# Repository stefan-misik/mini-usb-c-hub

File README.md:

# Mini USB-C Hub

Miniature USB-C hub to attach to your keyboard so you can share one wire for
mouse and keyboard. This hub uses FE1.1s USB 2.0 hub IC.

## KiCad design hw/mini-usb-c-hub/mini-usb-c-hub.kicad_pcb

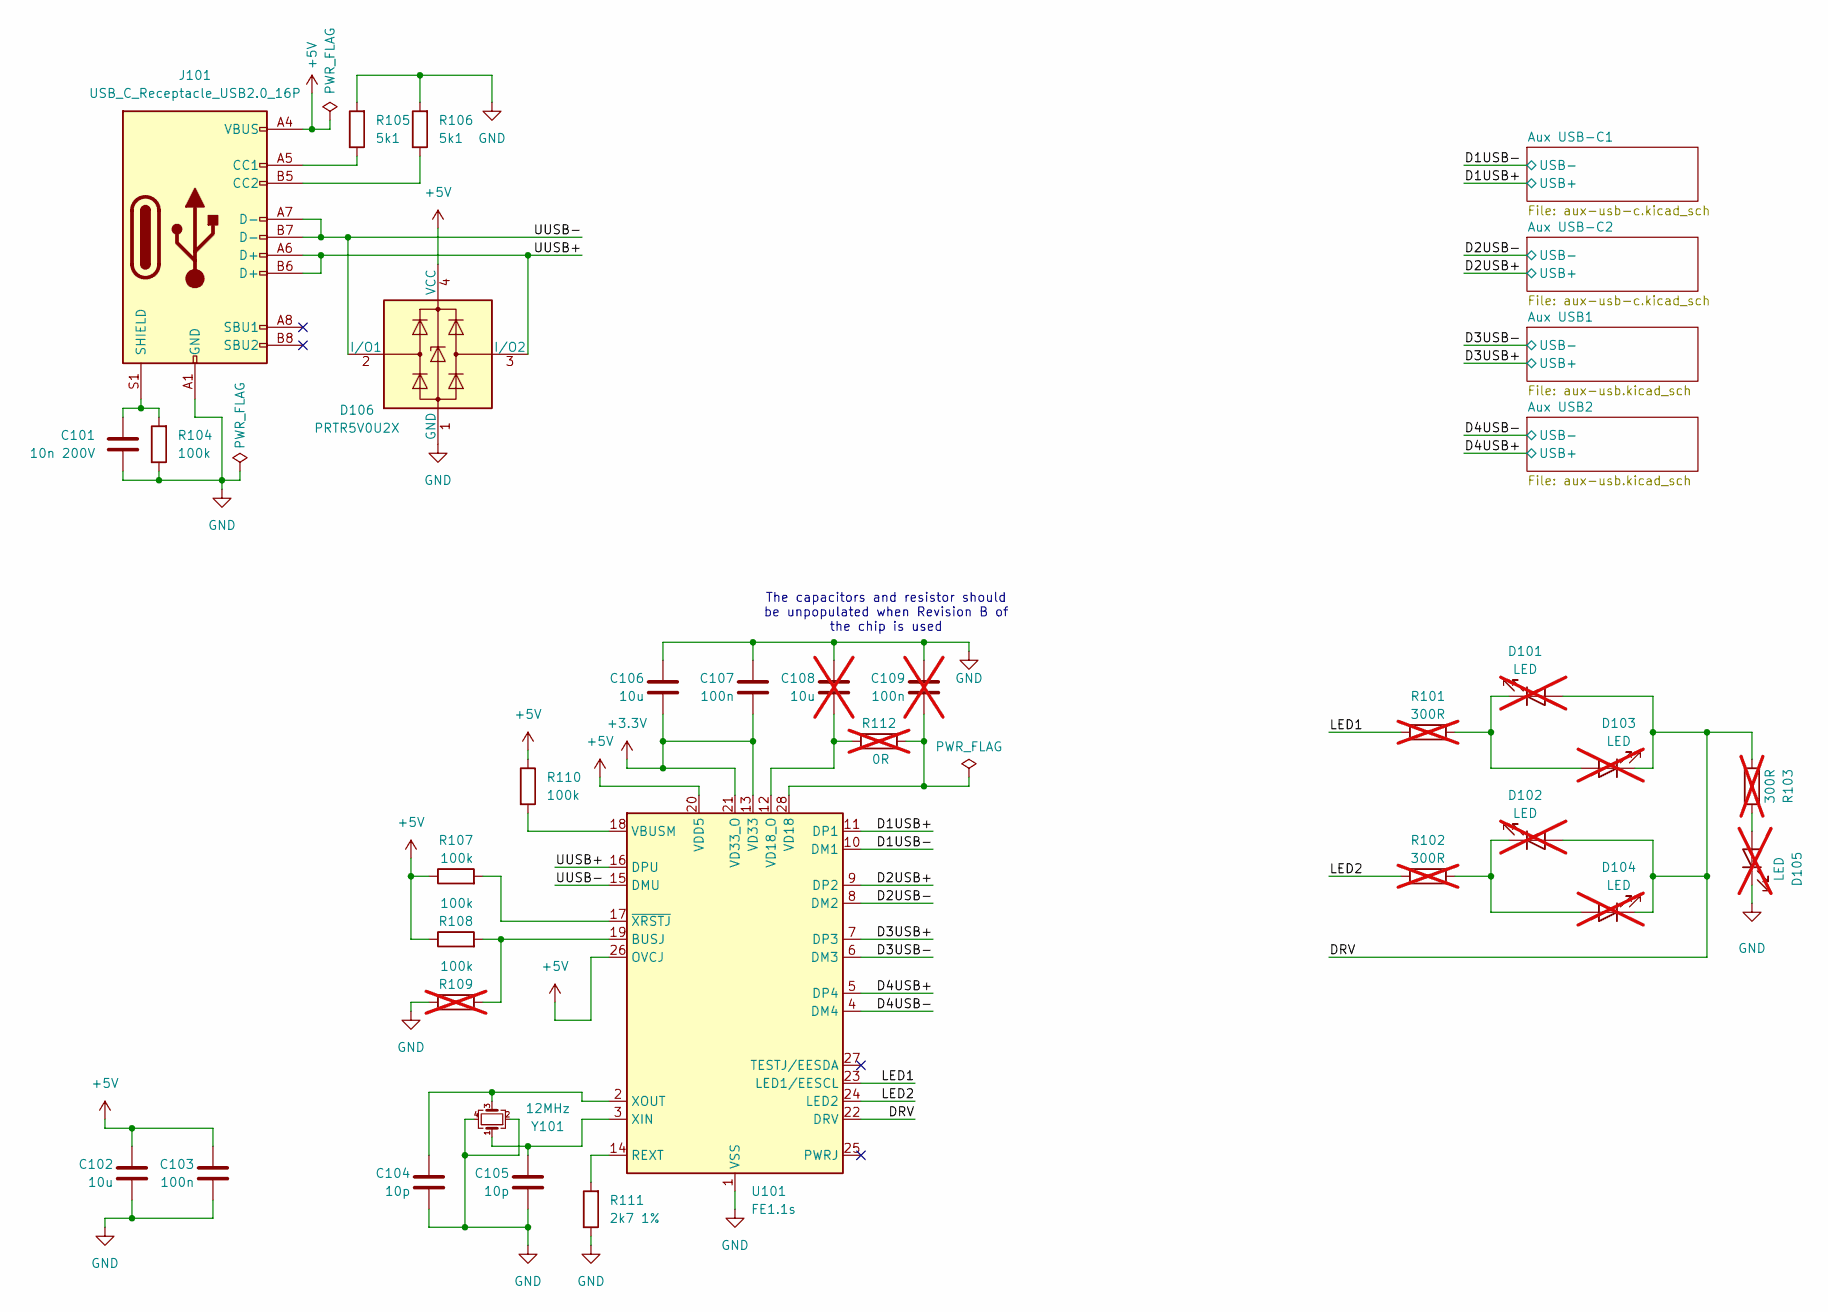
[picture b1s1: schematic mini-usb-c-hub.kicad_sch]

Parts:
C101: 10n 200V; C_0805_2012Metric_Pad1.18x1.45mm_HandSolder
C102, C106: 10u; C_1206_3216Metric_Pad1.33x1.80mm_HandSolder
C103, C107: 100n; C_0805_2012Metric_Pad1.18x1.45mm_HandSolder
C104, C105: 10p; C_0805_2012Metric_Pad1.18x1.45mm_HandSolder
C108: 10u; C_1206_3216Metric_Pad1.33x1.80mm_HandSolder; not fitted
C109: 100n; C_0805_2012Metric_Pad1.18x1.45mm_HandSolder; not fitted
D101, D102, D103, D104, D105: LED; LED_0805_2012Metric_Pad1.15x1.40mm_HandSolder; not fitted
D106: PRTR5V0U2X; SOT-143
J101: USB_C_Receptacle_USB2.0_16P; USB_C_Receptacle_G-Switch_GT-USB-7010ASV_shortened
R101, R102, R103: 300R; R_0805_2012Metric_Pad1.20x1.40mm_HandSolder; not fitted
R104, R107, R108, R110: 100k; R_0805_2012Metric_Pad1.20x1.40mm_HandSolder
R105, R106: 5k1; R_0805_2012Metric_Pad1.20x1.40mm_HandSolder
R109: 100k; R_0805_2012Metric_Pad1.20x1.40mm_HandSolder; not fitted
R111: 2k7 1%; R_0805_2012Metric_Pad1.20x1.40mm_HandSolder
R112: 0R; R_0805_2012Metric_Pad1.20x1.40mm_HandSolder; not fitted
U101: FE1.1s; SSOP-28_3.9x9.9mm_P0.635mm
Y101: 12MHz; Crystal_SMD_3225-4Pin_3.2x2.5mm_HandSoldering

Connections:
+3.3V: C106.1, C107.1, U101.13 (VD33), U101.21 (VD33_O)
+5V: C102.2, C103.2, D106.4 (VCC), J101.A4 (VBUS), J101.A9 (VBUS), J101.B4 (VBUS), J101.B9 (VBUS), R107.1, R108.1, R110.1, U101.20 (VDD5), U101.26 (OVCJ); also elsewhere on the board
/D1USB+: U101.11 (DP1); also elsewhere on the board
/D1USB-: U101.10 (DM1); also elsewhere on the board
/D2USB+: U101.9 (DP2); also elsewhere on the board
/D2USB-: U101.8 (DM2); also elsewhere on the board
/D3USB+: U101.7 (DP3); also elsewhere on the board
/D3USB-: U101.6 (DM3); also elsewhere on the board
/D4USB+: U101.5 (DP4); also elsewhere on the board
/D4USB-: U101.4 (DM4); also elsewhere on the board
/DRV: D101.2 (A), D102.2 (A), D103.1 (K), D104.1 (K), R103.1, U101.22 (DRV)
/LED1: R101.1, U101.23 (LED1/EESCL)
/LED2: R102.1, U101.24 (LED2)
/UUSB+: D106.3 (I/O2), J101.A6 (D+), J101.B6 (D+), U101.16 (DPU)
/UUSB-: D106.2 (I/O1), J101.A7 (D-), J101.B7 (D-), U101.15 (DMU)
GND: C101.1, C102.1, C103.1, C104.1, C105.1, C106.2, C107.2, C108.2, C109.2, D105.1 (K), D106.1 (GND), J101.A1 (GND), J101.A12 (GND), J101.B1 (GND), J101.B12 (GND), R104.1, R105.2, R106.2, R109.1, R111.1, U101.1 (VSS), Y101.2, Y101.4; also elsewhere on the board
unnamed: D101.1 (K), D103.2 (A), R101.2
unnamed: D102.1 (K), D104.2 (A), R102.2
unnamed: D105.2 (A), R103.2
unnamed: J101.A5 (CC1), R105.1
unnamed: J101.B5 (CC2), R106.1
unnamed: C101.2, J101.S1 (SHIELD), R104.2
unnamed: R108.2, R109.2, U101.19 (BUSJ)
unnamed: R111.2, U101.14 (REXT)
unnamed: R110.2, U101.18 (VBUSM)
unnamed: C109.1, R112.2, U101.28 (VD18)
unnamed: C108.1, R112.1, U101.12 (VD18_O)
unnamed: C105.2, U101.3 (XIN), Y101.1
unnamed: C104.2, U101.2 (XOUT), Y101.3
unnamed: R107.2, U101.17 (~XRSTJ)

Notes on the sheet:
The capacitors and resistor should be unpopulated when Revision B of the chip is used

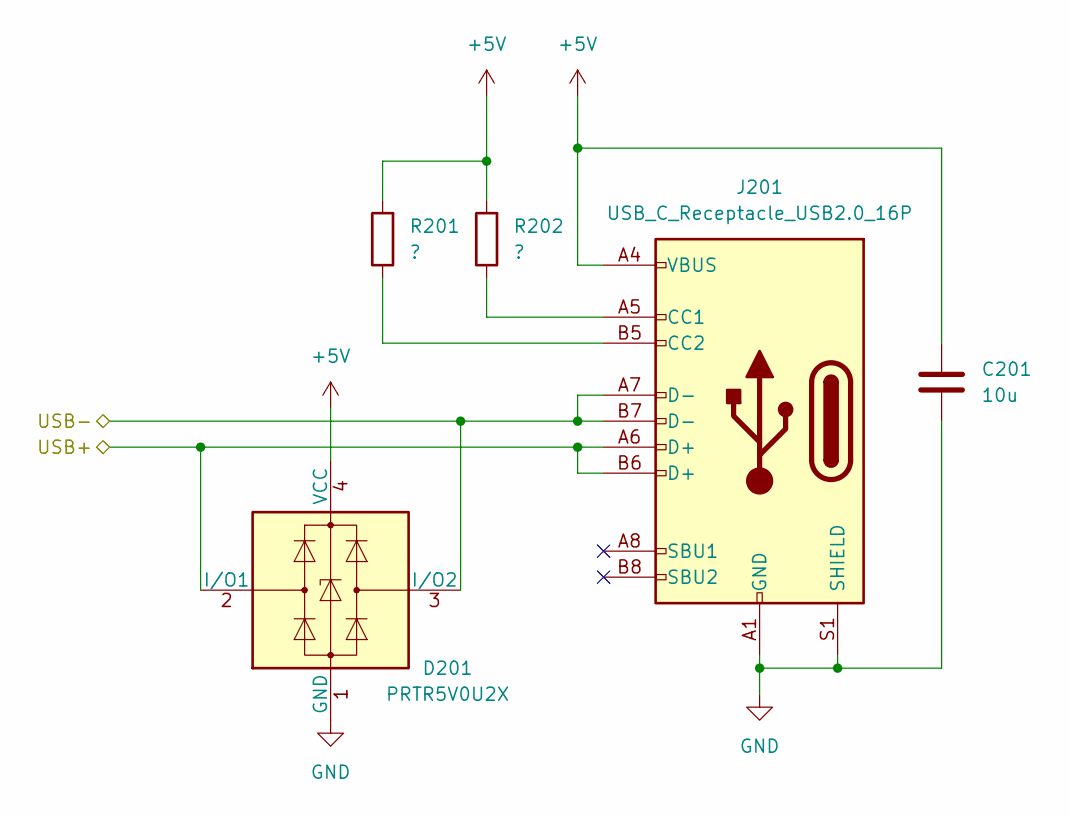
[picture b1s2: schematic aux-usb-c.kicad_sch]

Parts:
C201: 10u; C_1206_3216Metric_Pad1.33x1.80mm_HandSolder
D201: PRTR5V0U2X; SOT-143
J201: USB_C_Receptacle_USB2.0_16P; USB_C_Receptacle_G-Switch_GT-USB-7010ASV_shortened
R201, R202: ?; R_0805_2012Metric_Pad1.20x1.40mm_HandSolder

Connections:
+5V: C201.1, D201.4 (VCC), J201.A4 (VBUS), J201.A9 (VBUS), J201.B4 (VBUS), J201.B9 (VBUS), R201.2, R202.2; also elsewhere on the board
/D1USB+: D201.2 (I/O1), J201.A6 (D+), J201.B6 (D+); also elsewhere on the board
/D1USB-: D201.3 (I/O2), J201.A7 (D-), J201.B7 (D-); also elsewhere on the board
GND: C201.2, D201.1 (GND), J201.A1 (GND), J201.A12 (GND), J201.B1 (GND), J201.B12 (GND), J201.S1 (SHIELD); also elsewhere on the board
unnamed: J201.A5 (CC1), R202.1
unnamed: J201.B5 (CC2), R201.1

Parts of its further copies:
C301: 10u; C_1206_3216Metric_Pad1.33x1.80mm_HandSolder
D301: PRTR5V0U2X; SOT-143
J301: USB_C_Receptacle_USB2.0_16P; USB_C_Receptacle_G-Switch_GT-USB-7010ASV_shortened
R301, R302: ?; R_0805_2012Metric_Pad1.20x1.40mm_HandSolder

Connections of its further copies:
+5V: C301.1, D301.4 (VCC), J301.A4 (VBUS), J301.A9 (VBUS), J301.B4 (VBUS), J301.B9 (VBUS), R301.2, R302.2; also elsewhere on the board
/D2USB+: D301.2 (I/O1), J301.A6 (D+), J301.B6 (D+); also elsewhere on the board
/D2USB-: D301.3 (I/O2), J301.A7 (D-), J301.B7 (D-); also elsewhere on the board
GND: C301.2, D301.1 (GND), J301.A1 (GND), J301.A12 (GND), J301.B1 (GND), J301.B12 (GND), J301.S1 (SHIELD); also elsewhere on the board
unnamed: J301.A5 (CC1), R302.1
unnamed: J301.B5 (CC2), R301.1

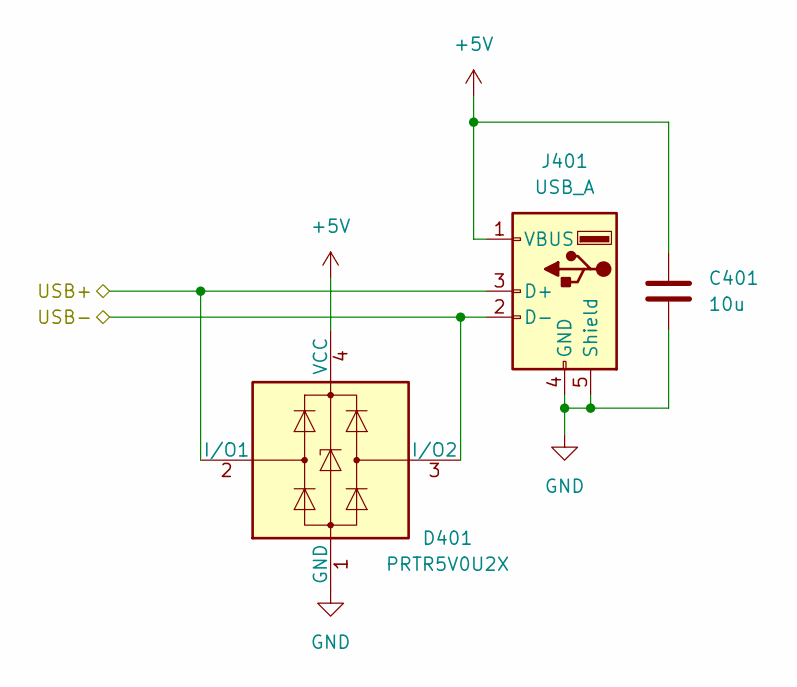
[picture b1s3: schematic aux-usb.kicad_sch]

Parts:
C401: 10u; C_1206_3216Metric_Pad1.33x1.80mm_HandSolder
D401: PRTR5V0U2X; SOT-143
J401: USB_A; USB_A_Molex_67643_Horizontal

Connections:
+5V: C401.1, D401.4 (VCC), J401.1 (VBUS); also elsewhere on the board
/D3USB+: D401.2 (I/O1), J401.3 (D+); also elsewhere on the board
/D3USB-: D401.3 (I/O2), J401.2 (D-); also elsewhere on the board
GND: C401.2, D401.1 (GND), J401.4 (GND), J401.5 (Shield); also elsewhere on the board

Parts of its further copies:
C501: 10u; C_1206_3216Metric_Pad1.33x1.80mm_HandSolder
D501: PRTR5V0U2X; SOT-143
J501: USB_A; USB_A_Molex_67643_Horizontal

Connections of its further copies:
+5V: C501.1, D501.4 (VCC), J501.1 (VBUS); also elsewhere on the board
/D4USB+: D501.2 (I/O1), J501.3 (D+); also elsewhere on the board
/D4USB-: D501.3 (I/O2), J501.2 (D-); also elsewhere on the board
GND: C501.2, D501.1 (GND), J501.4 (GND), J501.5 (Shield); also elsewhere on the board

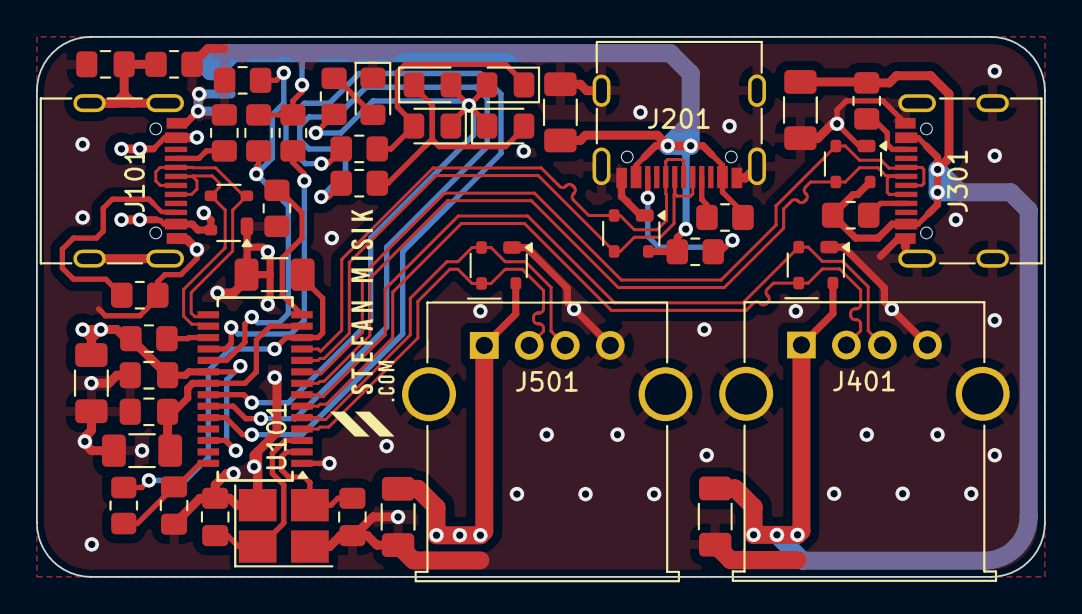
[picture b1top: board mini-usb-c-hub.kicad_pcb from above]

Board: 4 copper layers, 56.0 x 30.0 mm, 46 parts (0 on the bottom side), 34 nets.

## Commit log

2024-11-09 Initial Kicad project
2024-11-09 chore(hw): choose usb-c receptacle
2024-11-10 chore(hw): add data pins, move upstream connector
2024-11-11 chore(hw): preliminary hub chip connections
2024-11-12 chore(hw): update power supply and add some notes
2024-11-12 chore(hw): add downstream ports
2024-11-13 chore(hw): add USB-C plug symbol
2024-11-13 chore(hw): add USB-C plug footprint
2024-11-14 chore(hw): add some basic layout
2024-11-14 chore(hw): lay-out some differential pairs
2024-11-18 chore(hw): attempt to layout without one USB A
2024-11-18 chore(hw): layout support components
2024-11-21 chore(hw): layout around switch and add downstream USB-C
2024-11-22 chore(hw): improve layout
2024-11-22 chore(hw): replace USB-C plug with socket
2024-11-22 chore(hw): update layout, fix references
2024-11-23 chore(hw): first complete layout
2024-11-23 chore(hw): add panelization and fabrication files makefile
2024-11-23 chore(hw): add notes on impedance control
2024-11-23 fix(hw): fix file attributes
2024-12-01 refactor(hw): use 0.17 mm width for USB pairs
2024-12-06 refactor(hw): minor fixes
2024-12-16 refactor(hw): layout improvements
2024-12-19 Minor layout improvements
2025-03-12 chore(hw): switch to KiCad 9.0
